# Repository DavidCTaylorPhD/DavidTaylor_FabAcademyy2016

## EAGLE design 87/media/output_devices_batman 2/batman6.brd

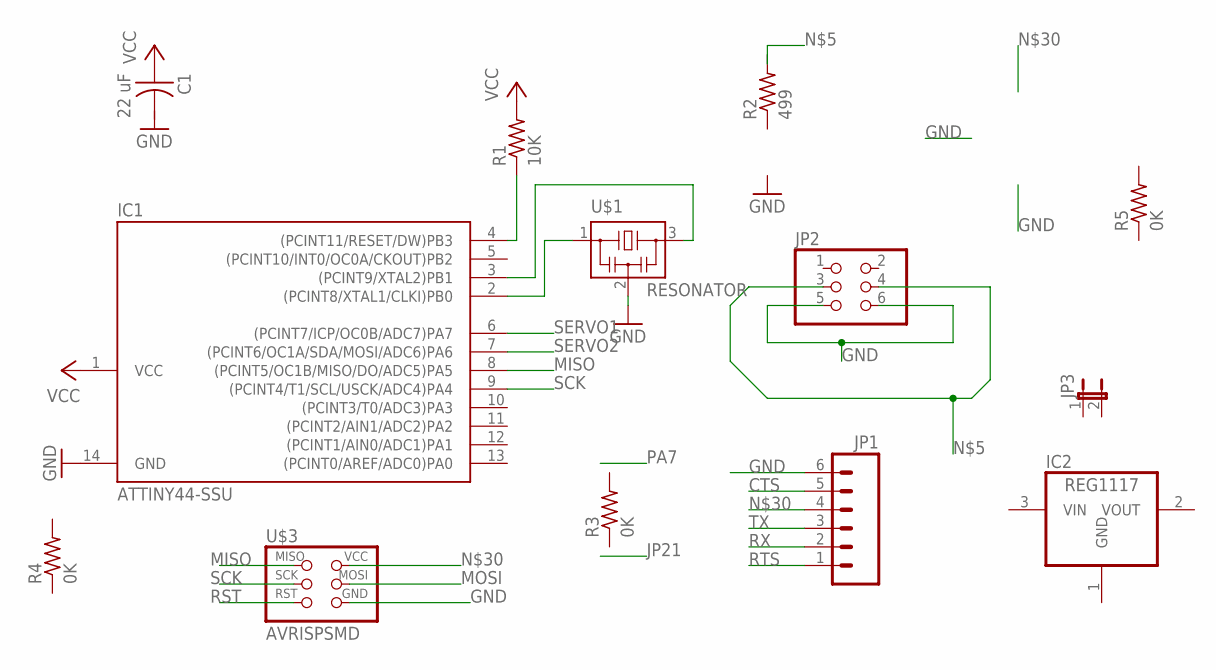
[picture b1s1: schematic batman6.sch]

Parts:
C1: 22 uF; C1206
IC1: ATTINY44-SSU; SOIC14
IC2: REG1117; SOT223
JP1: M06SMD; 1X06-SMD
JP2: PINHD-2X3-SMD; 2X03SMD
JP3: JP1E; JP1
R1: 10K; R1206
R2: 499; R1206
R3, R4, R5: 0K; R1206
U$1: RESONATOR; EFOBM
U$3: AVRISPSMD; 2X03SMD

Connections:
CTS: JP1.5
GND: IC1.14 (GND), IC2.1 (GND), JP1.6, JP2.5, JP2.6, U$1.2, U$3.6 (GND)
JP2: IC1.4 ((PCINT11/RESET/DW)PB3), R1.1
MISO: IC1.8 ((PCINT5/OC1B/MISO/DO/ADC5)PA5), U$3.1 (MISO)
MOSI: U$3.4 (MOSI)
unnamed: IC1.2 ((PCINT8/XTAL1/CLKI)PB0), U$1.1
unnamed: IC1.3 ((PCINT9/XTAL2)PB1), U$1.3
unnamed: JP2.3, JP2.4
unnamed: C1.1, IC1.1 (VCC), JP1.4, R1.2, U$3.2 (VCC)
RST: U$3.5 (RST)
RTS: JP1.1
RX: JP1.2
SCK: IC1.9 ((PCINT4/T1/SCL/USCK/ADC4)PA4), U$3.3 (SCK)
SERVO1: IC1.6 ((PCINT7/ICP/OC0B/ADC7)PA7)
SERVO2: IC1.7 ((PCINT6/OC1A/SDA/MOSI/ADC6)PA6)
TX: JP1.3

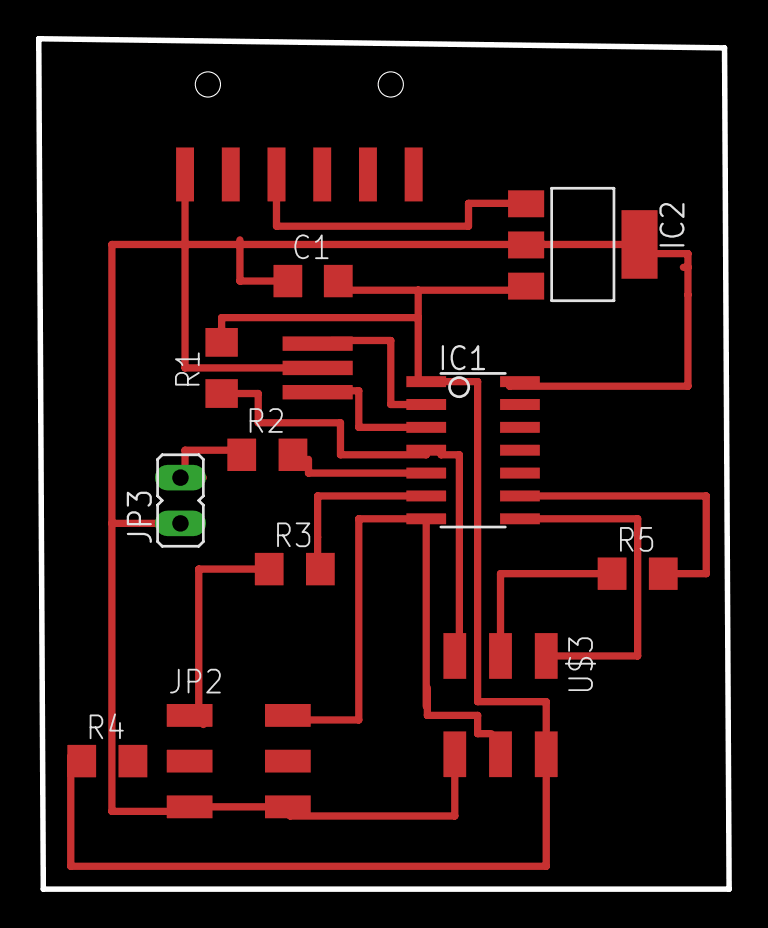
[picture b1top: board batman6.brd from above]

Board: 2 copper layers, 38.4 x 47.2 mm, 13 parts (0 on the bottom side), 8 nets.

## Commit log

2019-01-23 uploading files 1.23.18 fab academy 2018

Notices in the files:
parts and their libraries:
SparkFun: Licensing: CC v3.0 Share-Alike You are welcome to use this library for commercial purposes.
